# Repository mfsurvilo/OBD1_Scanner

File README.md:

# OBD1 Scanner

An ESP32-S3 based scanner for OBD-I era ECUs. The device hosts its own Wi-Fi
access point and serves a web console (PWA) straight off the chip — no app to
install — and updates itself over the internet with one button.

- **Firmware:** Arduino/ESP32-S3 (PlatformIO), FreeRTOS tasks, AP+STA Wi-Fi,
  OTA with bootloader rollback.
- **Console (PWA):** served from the device's LittleFS partition; live status
  over WebSocket, Wi-Fi provisioning, one-button update.
- **Delivery:** GitHub Releases hold the images; a static GitHub Pages page
  flashes a device over USB for recovery.

## How the pieces fit together

```
  ┌────────────┐   serves    ┌──────────────┐
  │  firmware  │ ──────────▶ │  PWA console │   (pwa_app/, flashed into LittleFS)
  │  (obd1)    │             │  obd1.local  │
  └─────┬──────┘             └──────┬───────┘
        │ heartbeat + /status       │ "Update now"
        │                           ▼
        │                    GET /update/check   ── picks highest release version
        │                    POST /update/pull   ── pulls firmware.bin + filesystem.bin
        ▼                                            from that release, flashes both
  GitHub Releases  ◀── build_release.sh / release.yml (firmware.bin, filesystem.bin, factory.bin)
        ▲
        │ mirrors factory.bin
  GitHub Pages flasher (firmware_server/flasher/)  ── USB recovery, version dropdown
```

Single sources of truth: `pwa_app/` is the only copy of the console, and
`firmware_server/flasher/versions.json` is the only list of published versions.

## Repo layout

| Path | What it is |
|---|---|
| `firmware/` | PlatformIO project — the device firmware, build/upload scripts, on-target tests |
| `pwa_app/` | The web console served from the device (flashed as the LittleFS image) |
| `firmware_server/` | The static USB-recovery flasher (GitHub Pages) — see its [README](firmware_server/README.md) |
| `tests/` | Host contract tests + hardware-in-the-loop scripts — see its [README](tests/README.md) |
| `protocol/`, `PROTOCOL.md` | OBD-I protocol notes |
| `board/` | KiCad hardware design |
| `developer_tools/` | Misc developer utilities |
| `CHANGELOG.md` | Per-version changes, split into Firmware / PWA sections |

## Quick start

**Flash a board over USB (developer):**
```bash
cd firmware && ./upload.sh          # builds + flashes firmware and the PWA image
```

**Use the device:** join Wi-Fi `OBD1_Scanner` (password `subaru92`), then open
`http://obd1.local/` (or `http://192.168.4.1/`).

## Flashing — three ways

1. **Developer USB** — `firmware/upload.sh` (one combined `pio` command: app + LittleFS).
2. **End-user USB recovery** — the GitHub Pages flasher: pick a version, connect,
   and flash the full image over WebSerial (desktop Chrome/Edge/Opera).
3. **Over-the-air** — the console's **Update now** button (details below).

## Updates (OTA)

The device updates itself over your home Wi-Fi — no file downloads:

1. In the console, save your home Wi-Fi credentials (**Internet update**).
2. Hit **Update now**. The firmware lists the repo's releases, picks the
   **highest version number** (it does *not* rely on GitHub's date-ordered
   `/releases/latest`), and pulls that release's `firmware.bin` (app) and
   `filesystem.bin` (PWA) by explicit tag.
3. It flashes both and reboots. A freshly-updated image boots on probation and
   must self-confirm healthy; if it doesn't, the bootloader rolls back to the
   previous slot.

## Releases

Each release publishes three stable-named assets (the git **tag** carries the
version): `firmware.bin` (app, OTA), `filesystem.bin` (PWA, OTA), and
`factory.bin` (full flash, USB recovery).

To cut a release:
```bash
git tag v0.5 && git push origin v0.5      # release.yml builds + publishes the assets
```
Then add the version to `firmware_server/flasher/versions.json` (newest first,
`latest: true` on it) and push to `master` so the Pages flasher lists it.

Full details — asset layout, the Pages CORS mirror, and the CI workflows — are
in **[`firmware_server/README.md`](firmware_server/README.md)**.

> Tip: cut and push one release tag at a time. Pushing a tag and a `master`
> change together can race the `release` and `pages` workflows.

## Testing

| Layer | What | Runs in CI? |
|---|---|---|
| 0 — host contract (`pytest`) | partition layout, `/status` + `/update/*` surface, image sizes, release-asset & `versions.json` contracts | ✅ |
| 1 — native unit (`pio test -e native`) | pure firmware logic — semver version ordering | ✅ |
| 4–5 — hardware (`hil_roundtrip.py`) | OTA app+fs round-trip, rollback, downgrade matrix | ❌ manual/local |

```bash
python -m pytest tests/ -q          # Layer 0, no hardware (what CI runs)
cd firmware && pio test -e native   # Layer 1, native Unity tests
```

Hardware tests need a real board on the `OBD1_Scanner` AP with USB attached.
Full commands and modes are in **[`tests/README.md`](tests/README.md)**.

## Building

```bash
cd firmware
./upload.sh                # build + USB-flash app + PWA
./build_release.sh         # build + package firmware.bin / filesystem.bin / factory.bin
pio run -e obd1            # just compile the firmware
```
Requires PlatformIO and `esptool` (both in the project `venv/`).

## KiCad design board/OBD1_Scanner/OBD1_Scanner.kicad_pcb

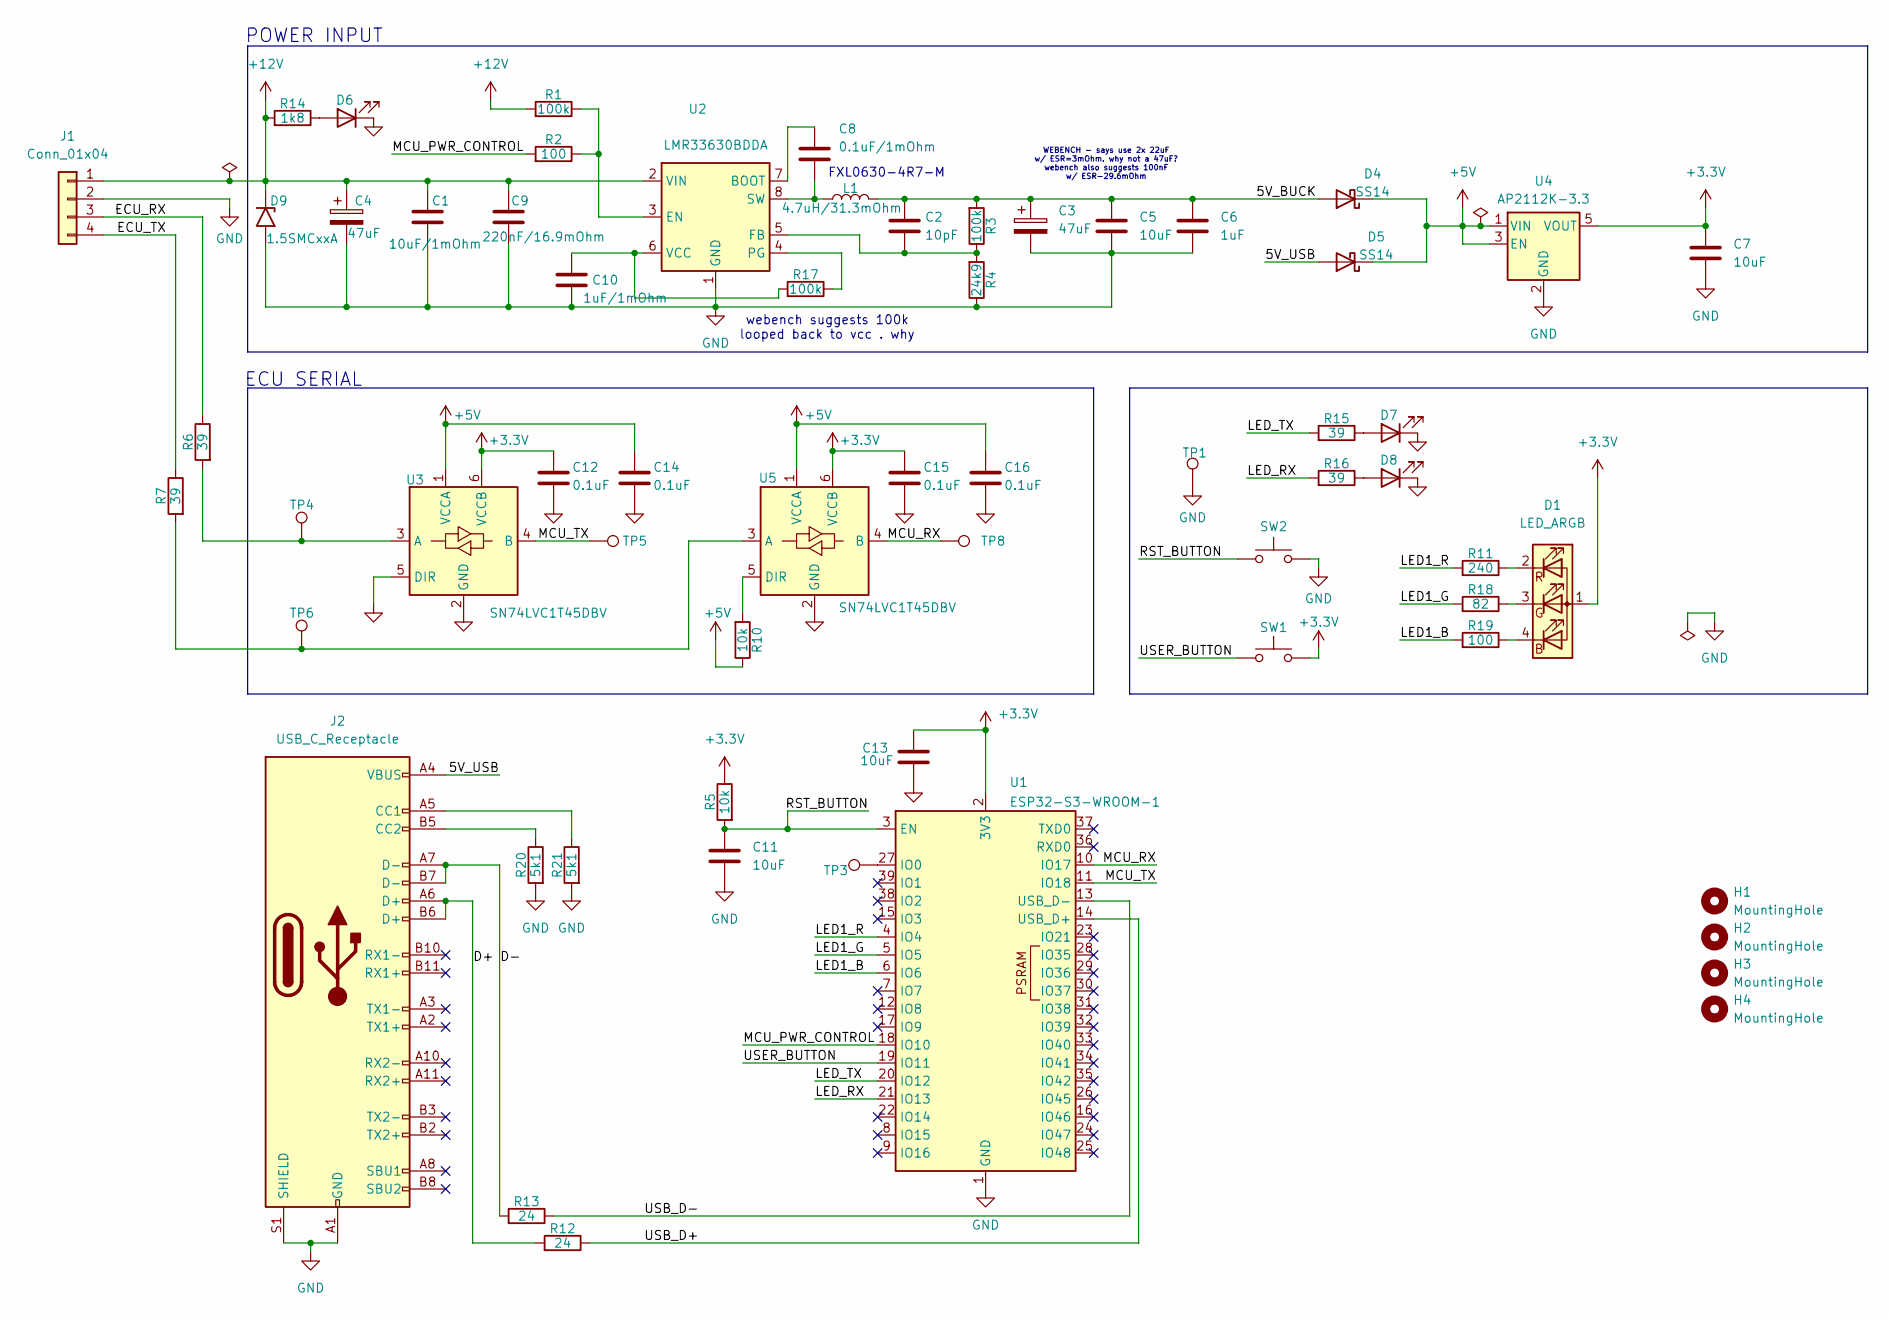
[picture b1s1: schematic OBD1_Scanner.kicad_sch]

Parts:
C1: 10uF/1mOhm; C_0603_1608Metric
C2: 10pF; C_0603_1608Metric
C3, C4: 47uF; CP_Elec_6.3x7.7
C5, C7, C11, C13: 10uF; C_0603_1608Metric
C6: 1uF; C_0603_1608Metric
C8: 0.1uF/1mOhm; C_0603_1608Metric
C9: 220nF/16.9mOhm; C_0603_1608Metric
C10: 1uF/1mOhm; C_0603_1608Metric
C12, C14, C15, C16: 0.1uF; C_0603_1608Metric
D1: LED_ARGB; LED_RGB_1210_C2890623
D4, D5: SS14; D_SMA
D6, D7, D8: LED; LED_0603_1608Metric_Pad1.05x0.95mm_HandSolder
D9: 1.5SMCxxA; D_SMC
H1, H2, H3, H4: MountingHole; MountingHole_3.2mm_M3_ISO7380_Pad_TopBottom
J1: Conn_01x04; Molex_Mini-Fit_Jr_5569-04A2_2x02_P4.20mm_Horizontal
J2: USB_C_Receptacle; USB_C_Receptacle_G-Switch_GT-USB-7010ASV
L1: 4.7uH/31.3mOhm; L_Changjiang_FXL0630
R1, R3, R17: 100k; R_0603_1608Metric; LCSC ^
R2, R19: 100; R_0603_1608Metric; LCSC ^
R4: 24k9; R_0603_1608Metric; LCSC ^
R5, R10: 10k; R_0603_1608Metric; LCSC ^
R6, R7, R15, R16: 39; R_0603_1608Metric; LCSC ^
R11: 240; R_0603_1608Metric; LCSC ^
R12, R13: 24; R_0603_1608Metric; LCSC ^
R14: 1k8; R_0603_1608Metric; LCSC ^
R18: 82; R_0603_1608Metric; LCSC ^
R20, R21: 5k1; R_0603_1608Metric; LCSC ^
SW1, SW2: SW_Push; SW_SPST_Panasonic_EVQPL_3PL_5PL_PT_A15
TP1, TP4, TP5, TP6, TP8: TestPoint; TestPoint_Loop_D2.60mm_Drill1.4mm_Beaded
TP3: TestPoint; TestPoint_Pad_1.5x1.5mm
U1: ESP32-S3-WROOM-1
U2: LMR33630BDDA; Texas_HSOP-8-1EP_3.9x4.9mm_P1.27mm_ThermalVias
U3, U5: SN74LVC1T45DBV; SOT-23-6
U4: AP2112K-3.3; SOT-23-5

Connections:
+3.3V: C7.1, C12.1, C13.1, C15.1, D1.1 (A), R5.2, SW1.2, U1.2 (3V3), U3.6 (VCCB), U4.5 (VOUT), U5.6 (VCCB)
+5V: C14.1, C16.1, D4.1 (K), D5.1 (K), R10.2, U3.1 (VCCA), U4.1 (VIN), U4.3 (EN), U5.1 (VCCA)
+12V: C1.1, C4.1, C9.1, D9.1 (A1), J1.1, R1.1, R14.1, U2.2 (VIN)
/5V_BUCK: C2.1, C3.1, C5.1, C6.1, D4.2 (A), L1.2, R3.1
/5V_USB: D5.2 (A), J2.A4 (VBUS), J2.A9 (VBUS), J2.B4 (VBUS), J2.B9 (VBUS)
/D+: J2.A6 (D+), J2.B6 (D+), R12.1
/D-: J2.A7 (D-), J2.B7 (D-), R13.1
/ECU_RX: J1.3, R6.2
/ECU_TX: J1.4, R7.2
/LED1_B: R19.1, U1.6 (IO6)
/LED1_G: R18.1, U1.5 (IO5)
/LED1_R: R11.1, U1.4 (IO4)
/LED_RX: R16.1, U1.21 (IO13)
/LED_TX: R15.1, U1.20 (IO12)
/MCU_PWR_CONTROL: R2.1, U1.18 (IO10)
/MCU_RX: TP8.1, U1.10 (IO17), U5.4 (B)
/MCU_TX: TP5.1, U1.11 (IO18), U3.4 (B)
/RST_BUTTON: C11.1, R5.1, SW2.1, U1.3 (EN)
/USB_D+: R12.2, U1.14 (USB_D+)
/USB_D-: R13.2, U1.13 (USB_D-)
/USER_BUTTON: SW1.1, U1.19 (IO11)
GND: C1.2, C3.2, C4.2, C5.2, C6.2, C7.2, C9.2, C10.2, C11.2, C12.2, C13.2, C14.2, C15.2, C16.2, D6.1 (K), D7.1 (K), D8.1 (K), D9.2 (A2), J1.2, J2.A1 (GND), J2.A12 (GND), J2.B1 (GND), J2.B12 (GND), J2.S1 (SHIELD), R4.2, R20.1, R21.1, SW2.2, TP1.1, U1.1 (GND), U1.40 (GND), U1.41 (GND), U2.1 (GND), U2.9 (GND), U3.2 (GND), U3.5 (DIR), U4.2 (GND), U5.2 (GND)
unnamed: D1.4 (BK), R19.2
unnamed: D1.3 (GK), R18.2
unnamed: D1.2 (RK), R11.2
unnamed: D6.2 (A), R14.2
unnamed: D7.2 (A), R15.2
unnamed: D8.2 (A), R16.2
unnamed: J2.A5 (CC1), R21.2
unnamed: J2.B5 (CC2), R20.2
unnamed: TP3.1, U1.27 (IO0)
unnamed: C8.1, U2.7 (BOOT)
unnamed: R1.2, R2.2, U2.3 (EN)
unnamed: C2.2, R3.2, R4.1, U2.5 (FB)
unnamed: R17.2, U2.4 (PG)
unnamed: C8.2, L1.1, U2.8 (SW)
unnamed: C10.1, R17.1, U2.6 (VCC)
unnamed: R6.1, TP4.1, U3.3 (A)
unnamed: R7.1, TP6.1, U5.3 (A)
unnamed: R10.1, U5.5 (DIR)

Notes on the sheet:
webench suggests 100k looped back to vcc . why
ECU SERIAL
POWER INPUT
FXL0630-4R7-M
WEBENCH - says use 2x 22uF w/ ESR=3mOhm. why not a 47uF? webench also suggests 100nF w/ ESR-29.6mOhm

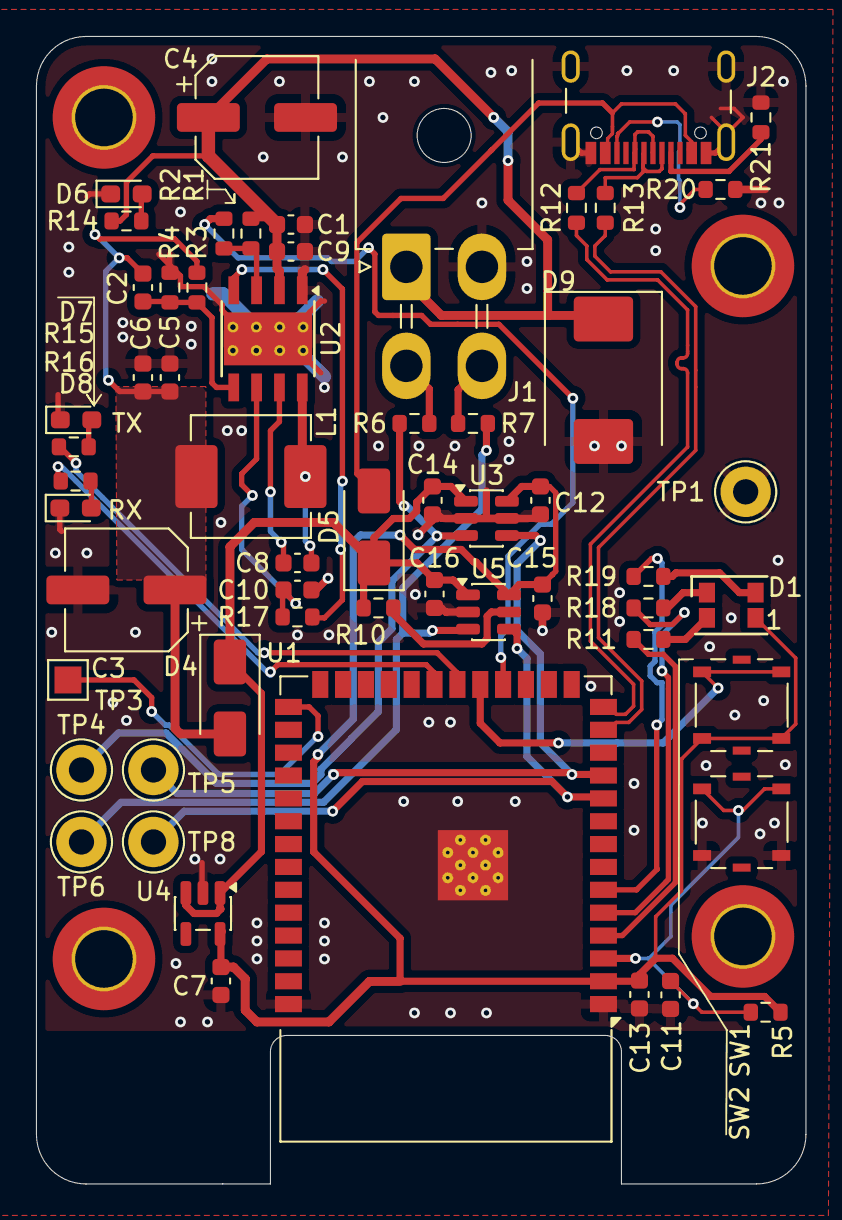
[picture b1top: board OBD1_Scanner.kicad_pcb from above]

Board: 2 copper layers, 42.8 x 63.8 mm, 62 parts (0 on the bottom side), 40 nets.

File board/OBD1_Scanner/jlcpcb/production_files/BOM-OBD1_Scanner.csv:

Comment,Designator,Footprint,LCSC,Quantity
0.1uF,"C12,C14,C15,C16",C_0603_1608Metric,C14663,4
0.1uF/1mOhm,C8,C_0603_1608Metric,C14663,1
1.5SMCxxA,D9,D_SMC,C522077,1
100,"R19,R2",R_0603_1608Metric,C22775,2
100k,"R1,R17,R3",R_0603_1608Metric,C25803,3
10k,"R10,R5",R_0603_1608Metric,C130232,2
10pF,C2,C_0603_1608Metric,C1634,1
10uF,"C11,C13,C5,C7",C_0603_1608Metric,C96446,4
10uF/1mOhm,C1,C_0603_1608Metric,C194427,1
1k8,R14,R_0603_1608Metric,C4177,1
1uF,C6,C_0603_1608Metric,C5673,1
1uF/1mOhm,C10,C_0603_1608Metric,C5673,1
220nF/16.9mOhm,C9,C_0603_1608Metric,C64705,1
24,"R12,R13",R_0603_1608Metric,C2907132,2
240,R11,R_0603_1608Metric,C23350,1
24k9,R4,R_0603_1608Metric,C861775,1
39,"R15,R16,R6,R7",R_0603_1608Metric,C23154,4
4.7uH/31.3mOhm,L1,L_Changjiang_FXL0630,C167220,1
47uF,"C3,C4",CP_Elec_6.3x7.7,C3349,2
5k1,"R20,R21",R_0603_1608Metric,C2907044,2
82,R18,R_0603_1608Metric,C23255,1
AP2112K-3.3,U4,SOT-23-5,C51118,1
Conn_01x04,J1,Molex_Mini-Fit_Jr_5569-04A2_2x02_P4.20mm_Horizontal,C5362279,1
ESP32-S3-WROOM-1,U1,ESP32-S3-WROOM-1,C2913198,1
LED,"D6,D7,D8",LED_0603_1608Metric_Pad1.05x0.95mm_HandSolder,C12624,3
LED_ARGB,D1,LED_RGB_1210_C2890623,C2890623,1
LMR33630BDDA,U2,Texas_HSOP-8-1EP_3.9x4.9mm_P1.27mm_ThermalVias,C544370,1
SN74LVC1T45DBV,"U3,U5",SOT-23-6,C7843,2
SS14,"D4,D5",D_SMA,C2480,2
SW_Push,"SW1,SW2",SW_SPST_Panasonic_EVQPL_3PL_5PL_PT_A15,C79172,2
TestPoint,"TP1,TP4,TP5,TP6,TP8",TestPoint_Loop_D2.60mm_Drill1.4mm_Beaded,C5277086,5
USB_C_Receptacle,J2,USB_C_Receptacle_G-Switch_GT-USB-7010ASV,C393939,1
TestPoint,TP3,TestPoint_Pad_1.5x1.5mm,,1

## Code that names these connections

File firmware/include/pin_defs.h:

#ifndef PIN_DEFS_H
#define PIN_DEFS_H

#include <Arduino.h>

//=============================================================================
// Pin Definitions  (ESP32-S3-WROOM-1 on the OBD1_Scanner board)
//=============================================================================

// Status RGB LED (LED1). Pins from the KiCad schematic nets LED1_R/G/B.
// NOTE: do NOT use GPIO 26-32 on the ESP32-S3 — they are wired to the internal
// SPI flash/PSRAM and driving them causes a flash watchdog reset.
static const uint8_t LED_GREEN = 4;   // IO4  (LED1_R)
static const uint8_t LED_BLUE  = 5;   // IO5  (LED1_G)
static const uint8_t LED_RED   = 6;   // IO6  (LED1_B)

// The RGB LED is COMMON-ANODE: the common pin sits at 3.3V, so a color lights
// when its GPIO is driven LOW (sinks current). HIGH = off.
static const uint8_t RGB_ON  = LOW;
static const uint8_t RGB_OFF = HIGH;

// TX/RX activity LEDs (nets LED_TX / LED_RX). Cathode to GND -> ACTIVE-HIGH.
static const uint8_t LED_TX_PIN = 12; // IO12 (LED_TX)
static const uint8_t LED_RX_PIN = 13; // IO13 (LED_RX)

//=============================================================================
// Serial
//=============================================================================
static const uint32_t DEBUG_BAUD = 115200;  // USB debug serial

#endif // PIN_DEFS_H

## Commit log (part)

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2026-05-14 beforeapp
2026-06-30 board-fab-v1
2026-06-30 misc
